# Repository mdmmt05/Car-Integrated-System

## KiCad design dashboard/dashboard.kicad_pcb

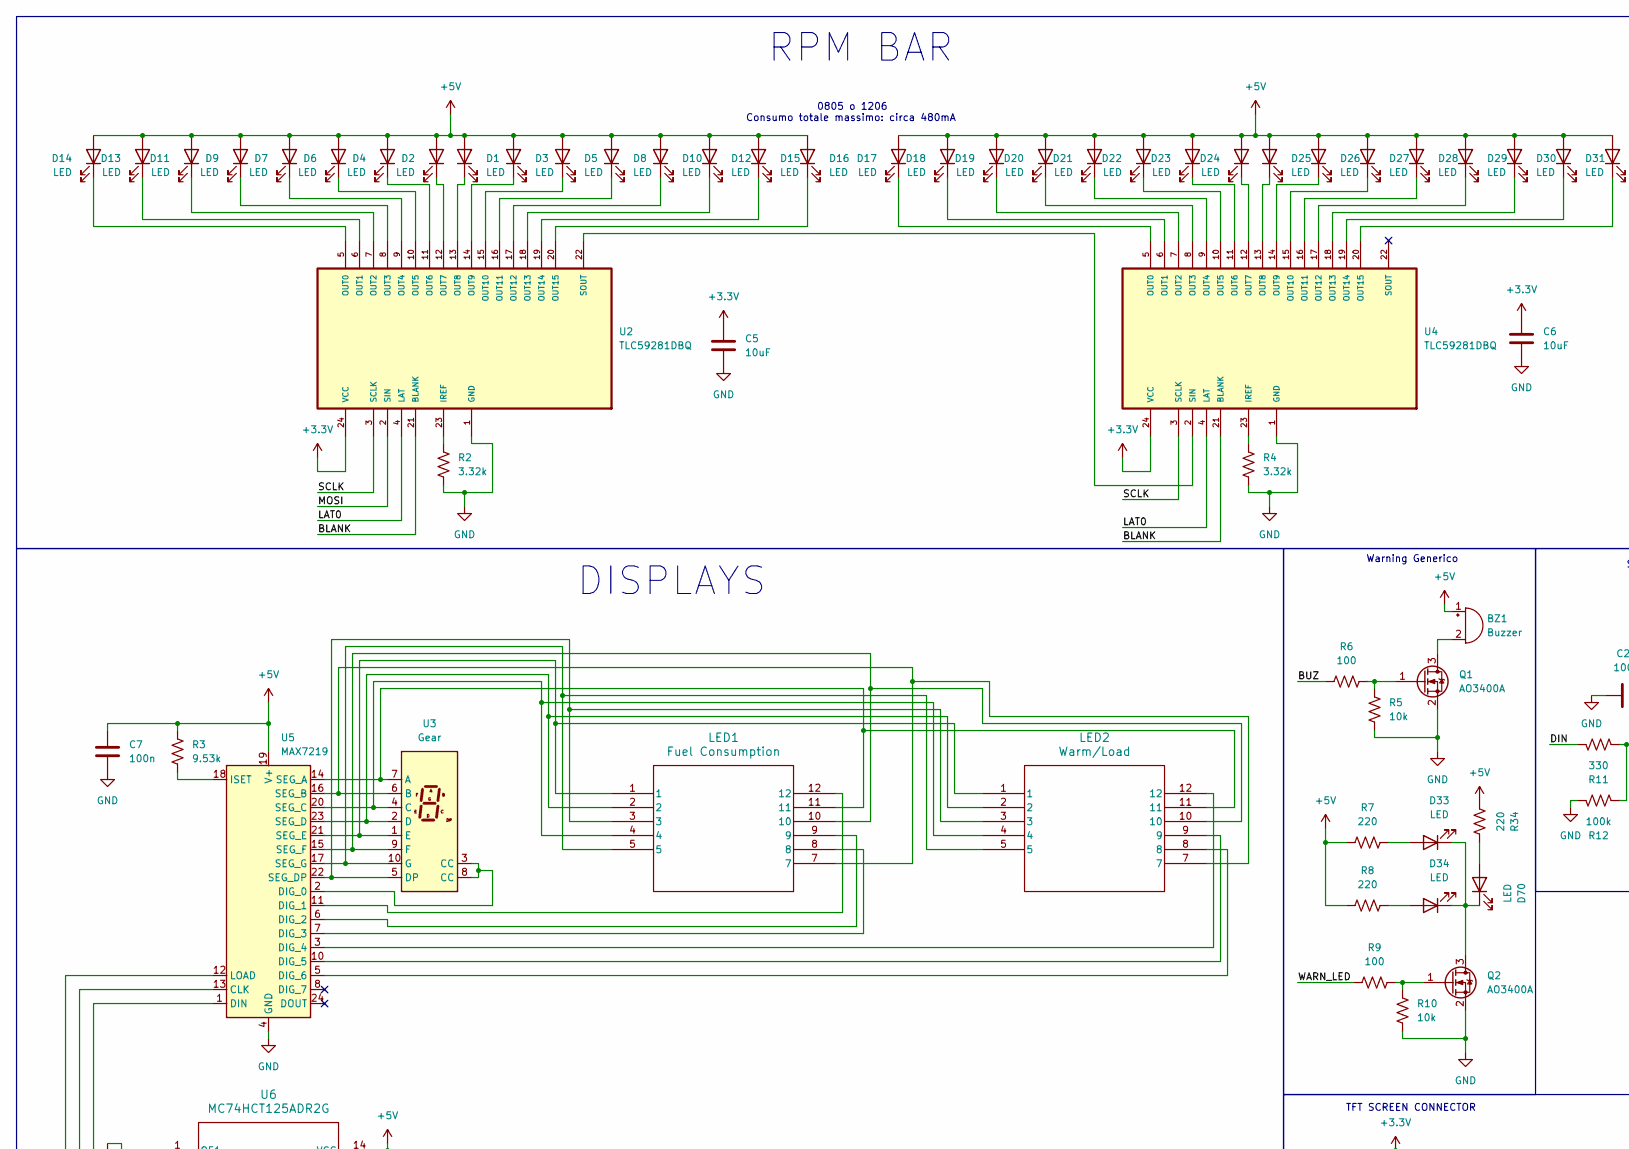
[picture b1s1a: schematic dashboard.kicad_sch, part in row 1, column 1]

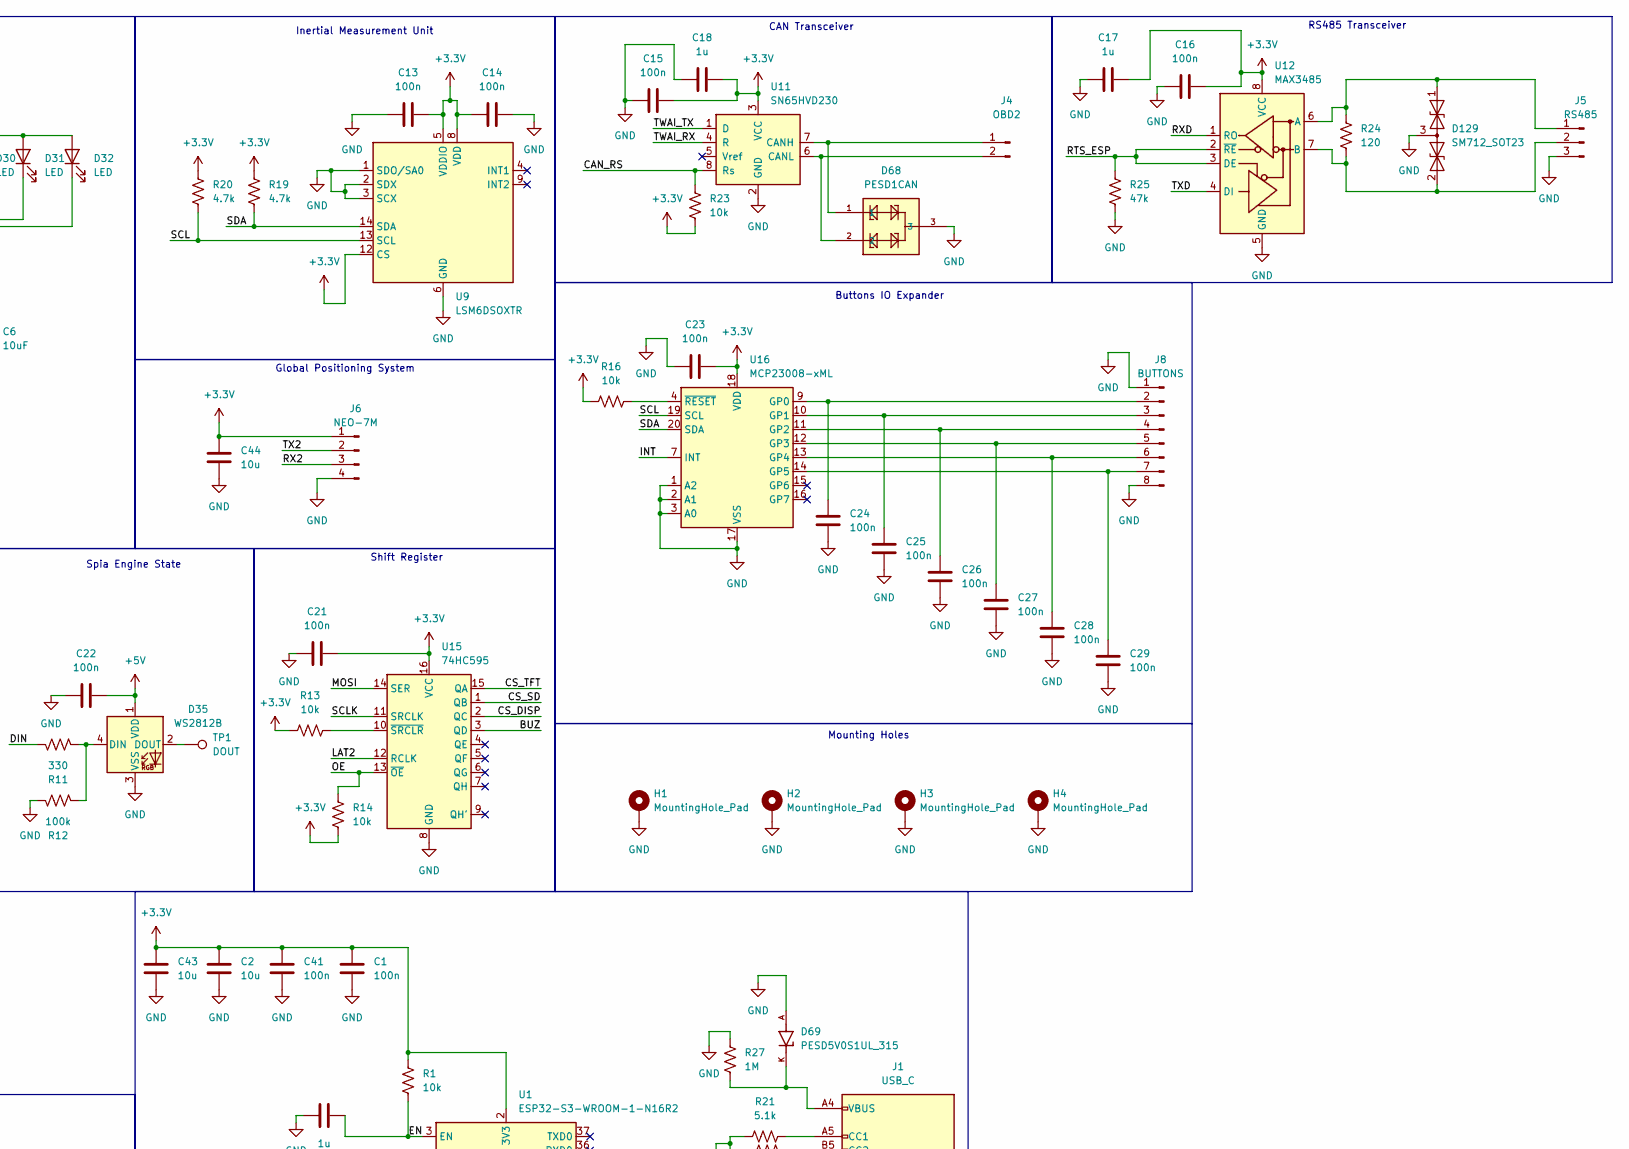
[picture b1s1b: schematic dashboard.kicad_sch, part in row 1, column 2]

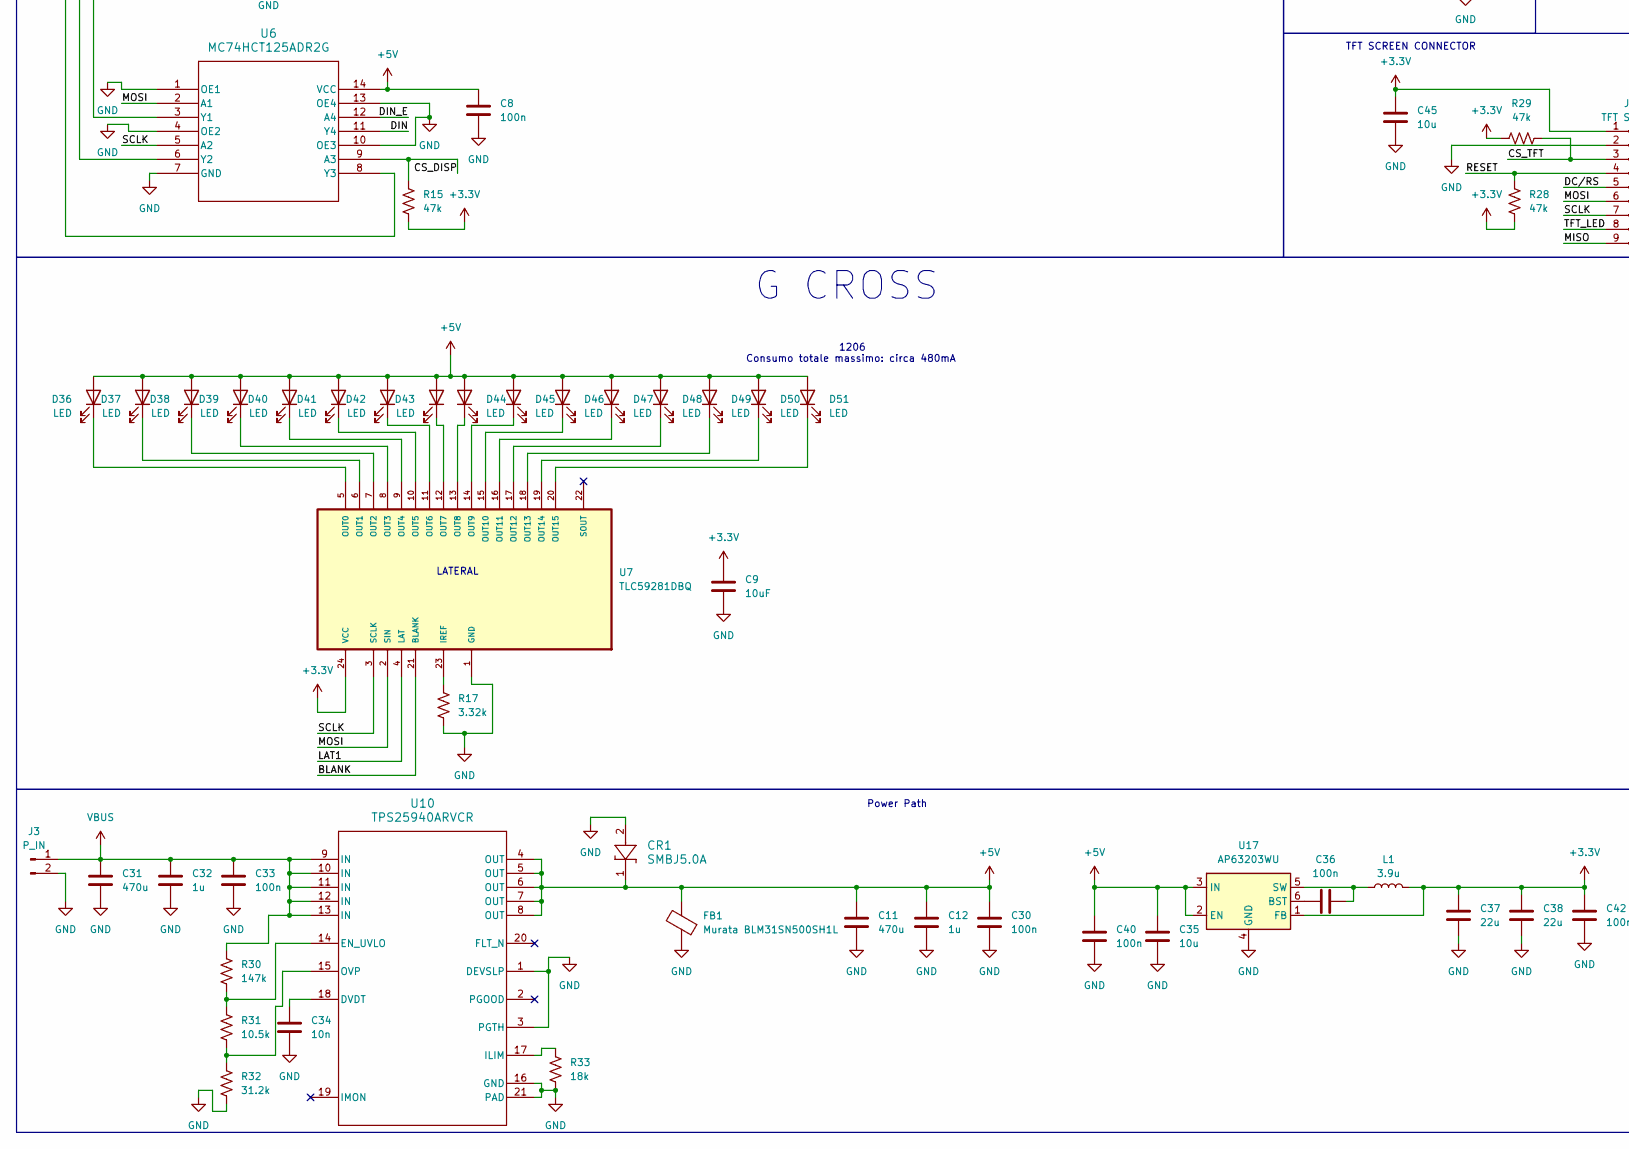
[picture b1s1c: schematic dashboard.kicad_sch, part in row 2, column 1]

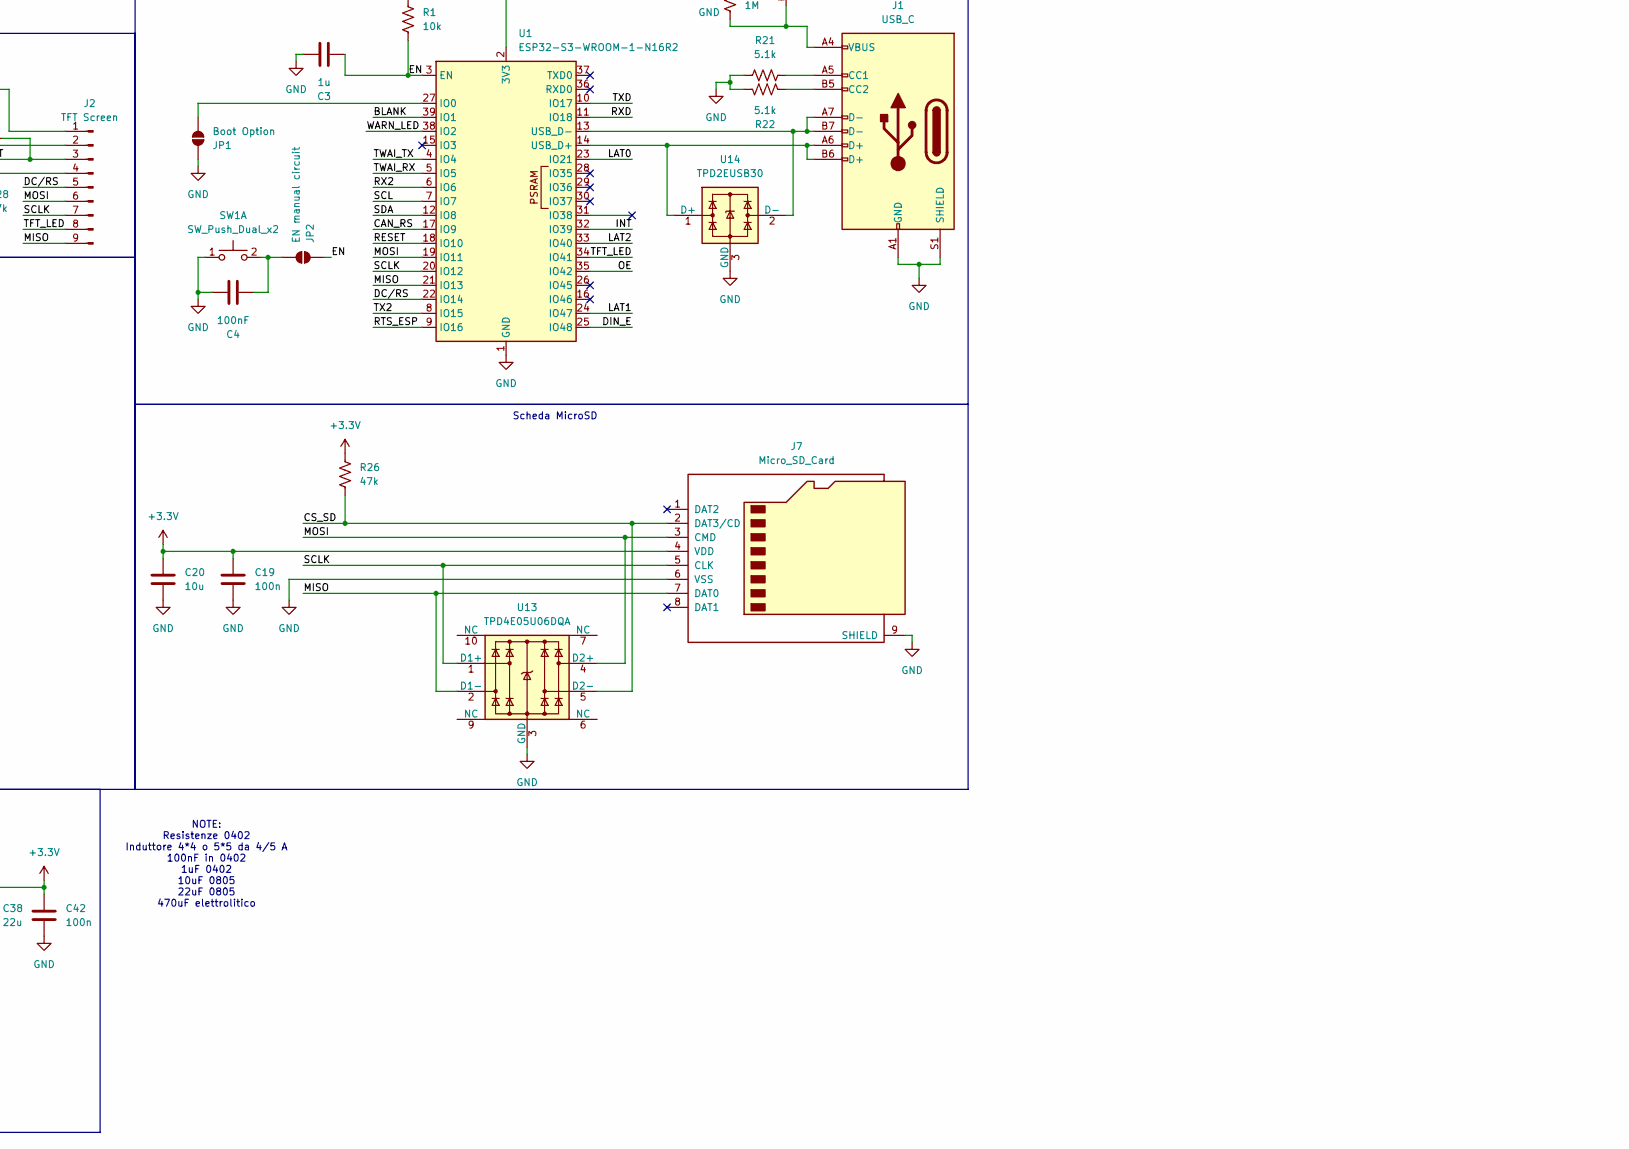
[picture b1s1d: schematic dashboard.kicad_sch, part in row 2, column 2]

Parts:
BZ1: Buzzer; Buzzer_12x9.5RM7.6
C1, C7, C8, C13, C14, C15, C16, C19, C21, C22, C23, C24, C25, C26, C27, C28, C29, C30, C33, C36, C40, C41, C42: 100n; C_0402_1005Metric
C2, C20, C35, C43, C44, C45: 10u; C_0805_2012Metric
C3, C12, C17, C18, C32: 1u; C_0402_1005Metric
C4: 100nF; C_0402_1005Metric
C5, C6, C9: 10uF; C_0805_2012Metric
C11, C31: 470u; CP_Elec_6.3x7.7
C34: 10n; C_0402_1005Metric
C37, C38: 22u; C_0805_2012Metric
CR1: SMBJ5.0A; D_SMB
D1, D2, D3, D4, D5, D6, D7, D8, D9, D10, D11, D12, D13, D14, D15, D16, D17, D18, D19, D20, D21, D22, D23, D24, D25, D26, D27, D28, D29, D30, D31, D32, D33, D34, D36, D37, D38, D39, D40, D41, D42, D43, D44, D45, D46, D47, D48, D49, D50, D51, D70: LED; LED_1206_3216Metric
D35: WS2812B; LED_WS2812B_PLCC4_5.0x5.0mm_P3.2mm
D68: PESD1CAN; SOT-23
D69: PESD5V0S1UL_315; DIO_PESD5V0S1UL_315
D129: SM712_SOT23; SOT-23
FB1: Murata BLM31SN500SH1L; C_1206_3216Metric
H1, H2, H3, H4: MountingHole_Pad; MountingHole_4.3mm_M4_Pad_Via
J1: USB_C; USB_C_Receptacle_JAE_DX07S016JA1R1500
J2: TFT Screen; PinHeader_1x09_P2.54mm_Vertical
J3: P_IN; TerminalBlock_MaiXu_MX126-5.0-02P_1x02_P5.00mm
J4: OBD2; TerminalBlock_MaiXu_MX126-5.0-02P_1x02_P5.00mm
J5: RS485; TerminalBlock_MaiXu_MX126-5.0-03P_1x03_P5.00mm
J6: NEO-7M; PinHeader_1x04_P2.54mm_Vertical
J7: Micro_SD_Card; microSD_HC_Molex_104031-0811
J8: BUTTONS; JST_XH_S8B-XH-A_1x08_P2.50mm_Horizontal
JP1: Boot Option; PinHeader_1x02_P2.54mm_Vertical
JP2: EN manual circuit; PinHeader_1x02_P2.54mm_Vertical
L1: 3.9u; L_Cenker_CKCS6045
LED1: Fuel Consumption; ZHIHAO FJ5361BH
LED2: Warm/Load; ZHIHAO FJ5361BH
Q1, Q2: AO3400A; SOT-23
R1, R5, R10, R13, R14, R16, R23: 10k; R_0402_1005Metric
R2, R4, R17: 3.32k; R_0402_1005Metric
R3: 9.53k; R_0402_1005Metric
R6, R9: 100; R_0402_1005Metric
R7, R8, R34: 220; R_0402_1005Metric
R11: 330; R_0402_1005Metric
R12: 100k; R_0402_1005Metric
R15, R25, R26, R28, R29: 47k; R_0402_1005Metric
R19, R20: 4.7k; R_0402_1005Metric
R21, R22: 5.1k; R_0402_1005Metric
R24: 120; R_0402_1005Metric
R27: 1M; R_0402_1005Metric
R30: 147k; R_0402_1005Metric
R31: 10.5k; R_0402_1005Metric
R32: 31.2k; R_0402_1005Metric
R33: 18k; R_0402_1005Metric
SW1: SW_Push_Dual_x2; SW_PUSH_6mm
TP1: DOUT; TestPoint_Pad_D2.0mm
U1: ESP32-S3-WROOM-1-N16R2; ESP32-S3-WROOM-1
U2, U4, U7: TLC59281DBQ; DBQ24; MPN TLC59281DBQ
U3: Gear; ARKLED SM411006N_15
U5: MAX7219; 21-0042_W24&plus_1_MXM
U6: MC74HCT125ADR2G; SOIC-14_NB_ONS
U9: LSM6DSOXTR; LGA-14_3x2.5mm_P0.5mm_LayoutBorder3x4y
U10: TPS25940ARVCR; RVC0020A
U11: SN65HVD230; SOIC-8_3.9x4.9mm_P1.27mm
U12: MAX3485; SOIC-8_3.9x4.9mm_P1.27mm
U13: TPD4E05U06DQA; USON-10_2.5x1.0mm_P0.5mm
U14: TPD2EUSB30; Texas_DRT-3
U15: 74HC595; SOIC127P600X175-16N
U16: MCP23008-xML; QFN-20-1EP_4x4mm_P0.5mm_EP2.7x2.7mm
U17: AP63203WU; TSOT-23-6

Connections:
+3.3V: C1.2, C2.2, C5.1, C6.1, C9.1, C13.2, C14.1, C15.2, C16.2, C17.2, C18.2, C19.1, C20.1, C21.2, C23.2, C37.1, C38.1, C41.2, C42.1, C43.2, C44.2, C45.2, J2.1, J6.1, J7.4 (VDD), L1.2, R1.2, R13.1, R14.1, R15.2, R16.1, R19.1, R20.1, R23.2, R26.1, R28.2, R29.1, U1.2 (3V3), U2.24 (VCC), U4.24 (VCC), U7.24 (VCC), U9.5 (VDDIO), U9.8 (VDD), U9.12 (CS), U11.3 (VCC), U12.8 (VCC), U15.16 (VCC), U16.18 (VDD), U17.1 (FB)
+5V: BZ1.1 (+), C7.1, C8.1, C11.1, C12.1, C22.2, C30.1, C35.1, C40.1, CR1.1, D1.2 (A), D2.2 (A), D3.2 (A), D4.2 (A), D5.2 (A), D6.2 (A), D7.2 (A), D8.2 (A), D9.2 (A), D10.2 (A), D11.2 (A), D12.2 (A), D13.2 (A), D14.2 (A), D15.2 (A), D16.2 (A), D17.2 (A), D18.2 (A), D19.2 (A), D20.2 (A), D21.2 (A), D22.2 (A), D23.2 (A), D24.2 (A), D25.2 (A), D26.2 (A), D27.2 (A), D28.2 (A), D29.2 (A), D30.2 (A), D31.2 (A), D32.2 (A), D35.1 (VDD), D36.2 (A), D37.2 (A), D38.2 (A), D39.2 (A), D40.2 (A), D41.2 (A), D42.2 (A), D43.2 (A), D44.2 (A), D45.2 (A), D46.2 (A), D47.2 (A), D48.2 (A), D49.2 (A), D50.2 (A), D51.2 (A), FB1.2, R3.1, R7.1, R8.1, R34.1, U5.19 (V+), U6.14 (VCC), U10.4 (OUT), U10.5 (OUT), U10.6 (OUT), U10.7 (OUT), U10.8 (OUT), U17.2 (EN), U17.3 (IN)
/BLANK: U1.39 (IO1), U2.21 (BLANK), U4.21 (BLANK), U7.21 (BLANK)
/BUZ: R6.1, U15.3 (QD)
/CAN_RS: R23.1, U1.17 (IO9), U11.8 (Rs)
/CS_DISP: R15.1, U6.9 (A3), U15.2 (QC)
/CS_SD: J7.2 (DAT3/CD), R26.2, U13.5 (D2-), U15.1 (QB)
/CS_TFT: J2.3, R29.2, U15.15 (QA)
/DC/RS: J2.5, U1.22 (IO14)
/DIN: R11.1, U6.11 (Y4)
/DIN_E: U1.25 (IO48), U6.12 (A4)
/EN: C3.1, JP2.1 (A), R1.1, U1.3 (EN)
/INT: U1.32 (IO39), U16.7 (INT)
/LAT0: U1.23 (IO21), U2.4 (LAT), U4.4 (LAT)
/LAT1: U1.24 (IO47), U7.4 (LAT)
/LAT2: U1.33 (IO40), U15.12 (RCLK)
/MISO: J2.9, J7.7 (DAT0), U1.21 (IO13), U13.2 (D1-)
/MOSI: J2.6, J7.3 (CMD), U1.19 (IO11), U2.2 (SIN), U6.2 (A1), U7.2 (SIN), U13.4 (D2+), U15.14 (SER)
/OE: R14.2, U1.35 (IO42), U15.13 (~OE)
/RESET: J2.4, R28.1, U1.18 (IO10)
/RTS_ESP: R25.1, U1.9 (IO16), U12.2 (~RE), U12.3 (DE)
/RX2: J6.3, U1.6 (IO6)
/RXD: U1.11 (IO18), U12.1 (RO)
/SCL: R20.2, U1.7 (IO7), U9.13 (SCL), U16.19 (SCL)
/SCLK: J2.7, J7.5 (CLK), U1.20 (IO12), U2.3 (SCLK), U4.3 (SCLK), U6.5 (A2), U7.3 (SCLK), U13.1 (D1+), U15.11 (SRCLK)
/SDA: R19.2, U1.12 (IO8), U9.14 (SDA), U16.20 (SDA)
/TFT_LED: J2.8, U1.34 (IO41)
/TWAI_RX: U1.5 (IO5), U11.4 (R)
/TWAI_TX: U1.4 (IO4), U11.1 (D)
/TX2: J6.2, U1.8 (IO15)
/TXD: U1.10 (IO17), U12.4 (DI)
/WARN_LED: R9.1, U1.38 (IO2)
GND: C1.1, C2.1, C3.2, C4.2, C5.2, C6.2, C7.2, C8.2, C9.2, C11.2, C12.2, C13.1, C14.2, C15.1, C16.1, C17.1, C18.1, C19.2, C20.2, C21.1, C22.1, C23.1, C24.1, C25.1, C26.1, C27.1, C28.1, C29.1, C30.2, C31.2, C32.2, C33.2, C34.2, C35.2, C37.2, C38.2, C40.2, C41.1, C42.2, C43.1, C44.1, C45.1, CR1.2, D35.3 (VSS), D68.3, D69.A, D129.3 (common), FB1.1, H1.1, H2.1, H3.1, H4.1, J1.A1 (GND), J1.A12 (GND), J1.B1 (GND), J1.B12 (GND), J1.S1 (SHIELD), J2.2, J3.2, J5.3, J6.4, J7.6 (VSS), J7.9 (SHIELD), J8.1, J8.8, JP1.1 (A), Q1.2 (S), Q2.2 (S), R2.2, R4.2, R5.2, R10.2, R12.1, R17.2, R21.1, R22.1, R25.2, R27.1, R32.2, R33.2, SW1.1 (C), U1.1 (GND), U1.40 (GND), U1.41 (GND), U2.1 (GND), U4.1 (GND), U5.4 (GND), U5.9 (GND), U6.1 (OE1), U6.4 (OE2), U6.7 (GND), U6.10 (OE3), U6.13 (OE4), U7.1 (GND), U9.1 (SDO/SA0), U9.2 (SDX), U9.3 (SCX), U9.6 (GND), U9.7 (GND), U10.1 (DEVSLP), U10.3 (PGTH), U10.16 (GND), U10.21 (PAD), U10.V, U11.2 (GND), U12.5 (GND), U13.3 (GND), U13.8 (GND), U14.3 (GND), U15.8 (GND), U16.1 (A2), U16.2 (A1), U16.3 (A0), U16.17 (VSS), U17.4 (GND)
unnamed: BZ1.2 (-), Q1.3 (D)
unnamed: D1.1 (K), U2.13 (OUT8)
unnamed: D2.1 (K), U2.12 (OUT7)
unnamed: D3.1 (K), U2.14 (OUT9)
unnamed: D4.1 (K), U2.11 (OUT6)
unnamed: D5.1 (K), U2.15 (OUT10)
unnamed: D6.1 (K), U2.10 (OUT5)
unnamed: D7.1 (K), U2.9 (OUT4)
unnamed: D8.1 (K), U2.16 (OUT11)
unnamed: D9.1 (K), U2.8 (OUT3)
unnamed: D10.1 (K), U2.17 (OUT12)
unnamed: D11.1 (K), U2.7 (OUT2)
unnamed: D12.1 (K), U2.18 (OUT13)
unnamed: D13.1 (K), U2.6 (OUT1)
unnamed: D14.1 (K), U2.5 (OUT0)
unnamed: D15.1 (K), U2.19 (OUT14)
unnamed: D16.1 (K), U2.20 (OUT15)
unnamed: D17.1 (K), U4.5 (OUT0)
unnamed: D18.1 (K), U4.6 (OUT1)
unnamed: D19.1 (K), U4.7 (OUT2)
unnamed: D20.1 (K), U4.8 (OUT3)
unnamed: D21.1 (K), U4.9 (OUT4)
unnamed: D22.1 (K), U4.10 (OUT5)
unnamed: D23.1 (K), U4.11 (OUT6)
unnamed: D24.1 (K), U4.12 (OUT7)
unnamed: D25.1 (K), U4.13 (OUT8)
unnamed: D26.1 (K), U4.14 (OUT9)
unnamed: D27.1 (K), U4.15 (OUT10)
unnamed: D28.1 (K), U4.16 (OUT11)
unnamed: D29.1 (K), U4.17 (OUT12)
unnamed: D30.1 (K), U4.18 (OUT13)
unnamed: D31.1 (K), U4.19 (OUT14)
unnamed: D32.1 (K), U4.20 (OUT15)
unnamed: D33.2 (A), R7.2
unnamed: D33.1 (K), D34.1 (K), D70.1 (K), Q2.3 (D)
unnamed: D34.2 (A), R8.2
unnamed: D35.4 (DIN), R11.2, R12.2
unnamed: D35.2 (DOUT), TP1.1
unnamed: D36.1 (K), U7.5 (OUT0)
unnamed: D37.1 (K), U7.6 (OUT1)
unnamed: D38.1 (K), U7.7 (OUT2)
unnamed: D39.1 (K), U7.8 (OUT3)
unnamed: D40.1 (K), U7.9 (OUT4)
unnamed: D41.1 (K), U7.10 (OUT5)
unnamed: D42.1 (K), U7.11 (OUT6)
unnamed: D43.1 (K), U7.12 (OUT7)
unnamed: D44.1 (K), U7.13 (OUT8)
unnamed: D45.1 (K), U7.14 (OUT9)
unnamed: D46.1 (K), U7.15 (OUT10)
unnamed: D47.1 (K), U7.16 (OUT11)
unnamed: D48.1 (K), U7.17 (OUT12)
unnamed: D49.1 (K), U7.18 (OUT13)
unnamed: D50.1 (K), U7.19 (OUT14)
unnamed: D51.1 (K), U7.20 (OUT15)
unnamed: D69.K, J1.A4 (VBUS), J1.A9 (VBUS), J1.B4 (VBUS), J1.B9 (VBUS), R27.2
unnamed: D70.2 (A), R34.2
unnamed: D129.1 (A1), J5.1, R24.1, U12.6 (A)
unnamed: D129.2 (A2), J5.2, R24.2, U12.7 (B)
unnamed: J1.A5 (CC1), R21.2
unnamed: J1.B5 (CC2), R22.2
unnamed: D68.1, J4.1, U11.7 (CANH)
unnamed: D68.2, J4.2, U11.6 (CANL)
unnamed: C24.2, J8.2, U16.9 (GP0)
unnamed: C25.2, J8.3, U16.10 (GP1)
unnamed: C26.2, J8.4, U16.11 (GP2)
unnamed: C27.2, J8.5, U16.12 (GP3)
unnamed: C28.2, J8.6, U16.13 (GP4)
unnamed: C29.2, J8.7, U16.14 (GP5)
unnamed: JP1.2 (B), U1.27 (IO0)
unnamed: C4.1, JP2.2 (B), SW1.2 (D)
unnamed: Q1.1 (G), R5.1, R6.2
unnamed: Q2.1 (G), R9.2, R10.1
unnamed: J1.A6 (D+), J1.B6 (D+), U1.14 (USB_D+), U14.1 (D+)
unnamed: J1.A7 (D-), J1.B7 (D-), U1.13 (USB_D-), U14.2 (D-)
unnamed: R2.1, U2.23 (IREF)
unnamed: U2.22 (SOUT), U4.2 (SIN)
unnamed: LED1.11, LED2.11, U3.7 (A), U5.14 (SEG_A)
unnamed: LED1.7, LED2.7, U3.6 (B), U5.16 (SEG_B)
unnamed: LED1.4, LED2.4, U3.4 (C), U5.20 (SEG_C)
unnamed: LED1.2, LED2.2, U3.2 (D), U5.23 (SEG_D)
unnamed: LED1.3, LED2.3, U3.5 (DP), U5.22 (SEG_DP)
unnamed: LED1.1, LED2.1, U3.1 (E), U5.21 (SEG_E)
unnamed: LED1.10, LED2.10, U3.9 (F), U5.15 (SEG_F)
unnamed: LED1.5, LED2.5, U3.10 (G), U5.17 (SEG_G)
unnamed: R4.1, U4.23 (IREF)
unnamed: U5.13 (CLK), U6.6 (Y2)
unnamed: U3.3 (CC), U3.8 (CC), U5.2 (DIG_0)
unnamed: LED1.12, U5.11 (DIG_1)
unnamed: LED1.9, U5.6 (DIG_2)
unnamed: LED1.8, U5.7 (DIG_3)
unnamed: LED2.12, U5.3 (DIG_4)
unnamed: LED2.9, U5.10 (DIG_5)
unnamed: LED2.8, U5.5 (DIG_6)
unnamed: U5.1 (DIN), U6.3 (Y1)
unnamed: R3.2, U5.18 (ISET)
unnamed: U5.12 (LOAD), U6.8 (Y3)
unnamed: R17.1, U7.23 (IREF)
unnamed: C34.1, U10.18 (DVDT)
unnamed: R30.2, R31.1, U10.14 (EN_UVLO)
unnamed: R33.1, U10.17 (ILIM)
unnamed: R31.2, R32.1, U10.15 (OVP)
unnamed: R13.2, U15.10 (~SRCLR)
unnamed: R16.2, U16.4 (~RESET)
unnamed: C36.1, U17.6 (BST)
unnamed: C36.2, L1.1, U17.5 (SW)
VBUS: C31.1, C32.1, C33.1, J3.1, R30.1, U10.9 (IN), U10.10 (IN), U10.11 (IN), U10.12 (IN), U10.13 (IN)

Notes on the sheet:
Consumo totale massimo: circa 480mA
Spia Engine State
Warning Generico
RS485 Transceiver
NOTE: Resistenze 0402 Induttore 4*4 o 5*5 da 4/5 A 100nF in 0402 1uF 0402 10uF 0805 22uF 0805 470uF elettrolitico
Global Positioning System
DISPLAYS
Buttons IO Expander
CAN Transceiver
1206
Power Path
Mounting Holes
RPM BAR
Scheda MicroSD
TFT SCREEN CONNECTOR
Shift Register
Inertial Measurement Unit
G CROSS
0805 o 1206
LATERAL

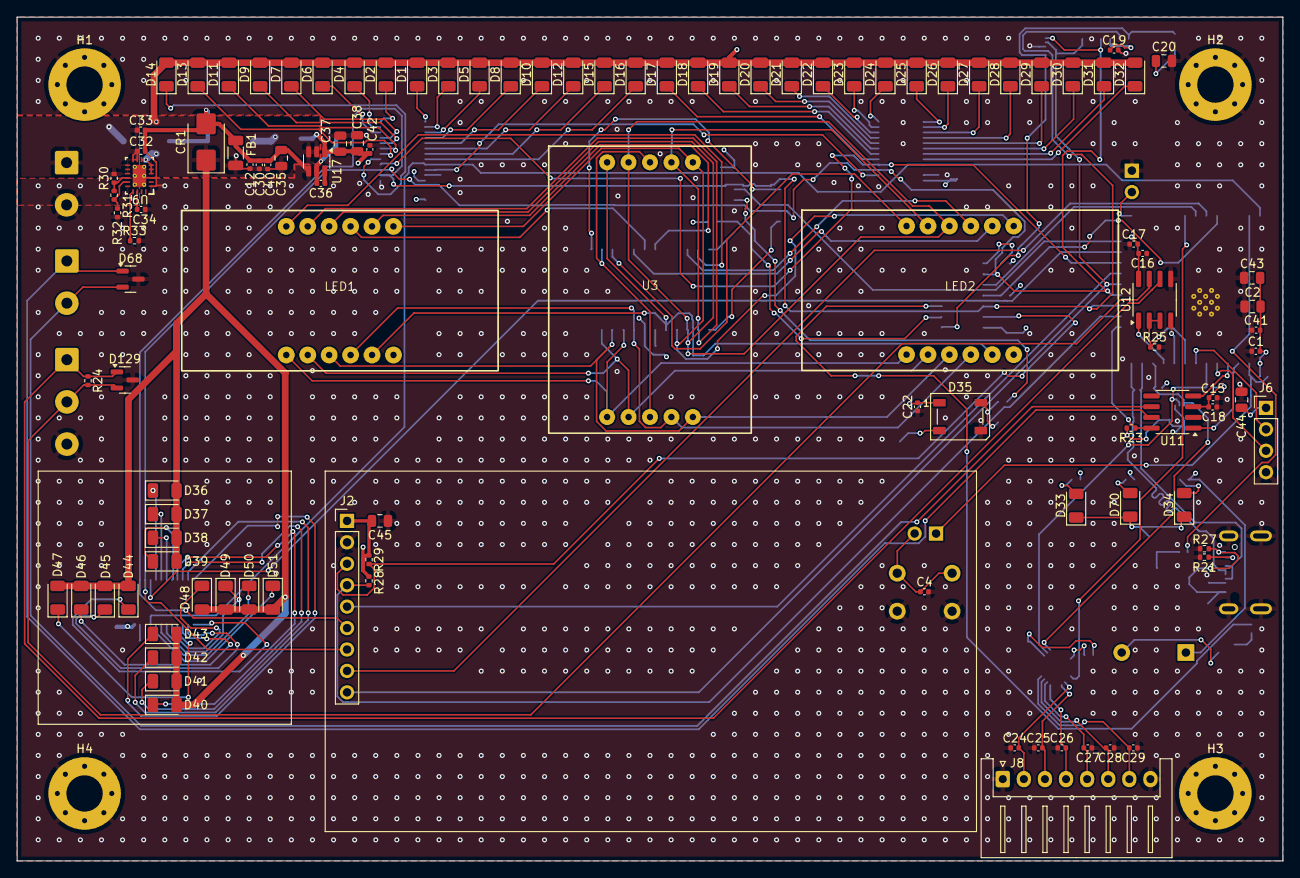
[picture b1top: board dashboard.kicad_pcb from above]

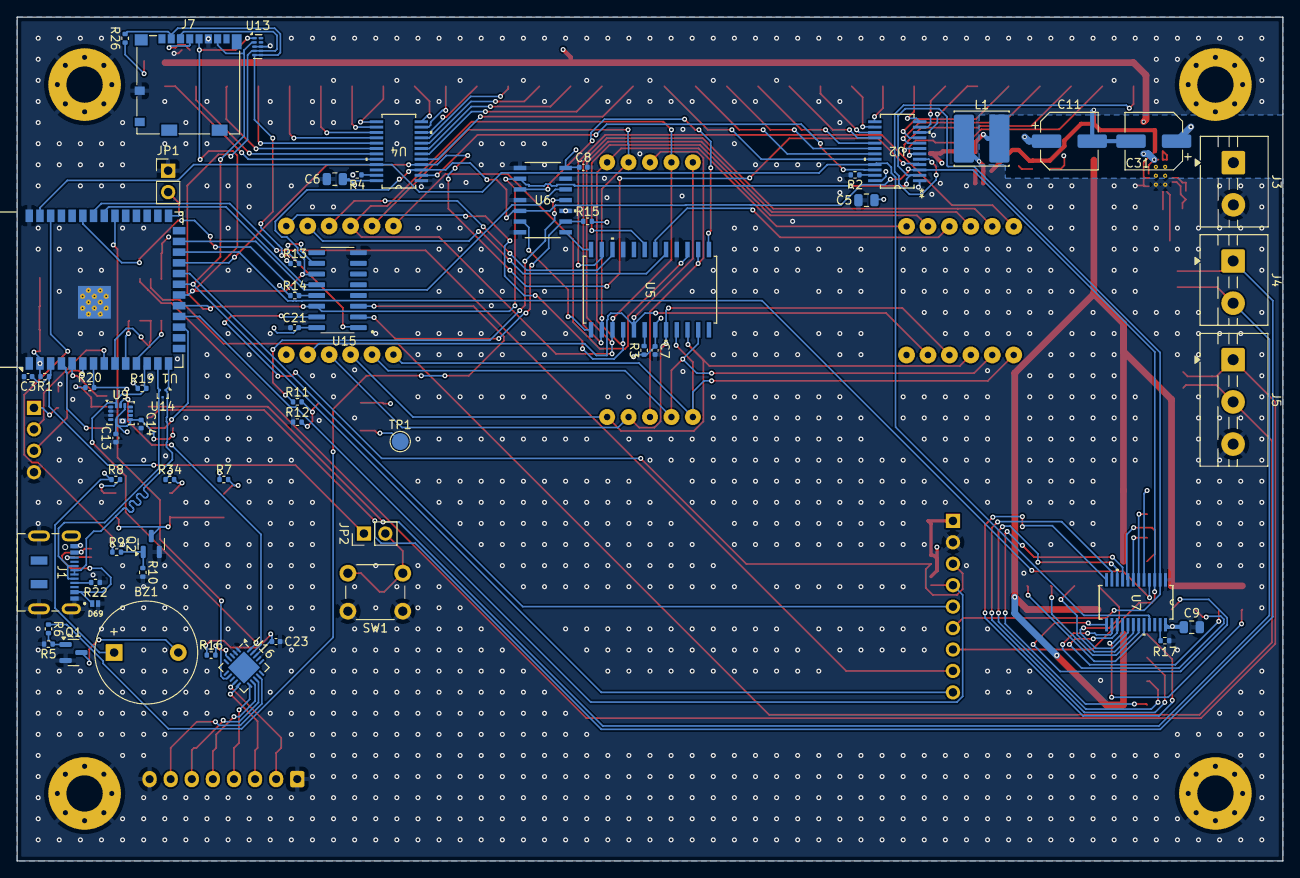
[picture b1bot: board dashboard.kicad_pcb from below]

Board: 4 copper layers, 150.0 x 100.0 mm, 171 parts (59 on the bottom side), 139 nets.

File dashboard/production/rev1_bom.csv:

Designator,Footprint,Quantity,Value,LCSC Part #
BZ1,Buzzer_12x9.5RM7.6,1,Buzzer,
"C1, C13, C14, C15, C16, C19, C21, C22, C23, C24, C25, C26, C27, C28, C29, C30, C33, C36, C40, C41, C42, C7, C8",0402,23,100n,
"C11, C31",CP_Elec_6.3x7.7,2,470u,
"C12, C17, C18, C3, C32",0402,5,1u,
"C2, C20, C35, C43, C44, C45",0805,6,10u,
C34,0402,1,10n,
"C37, C38",0805,2,22u,
C4,0402,1,100nF,
"C5, C6, C9",0805,3,10uF,
CR1,D_SMB,1,SMBJ5.0A,
"D1, D10, D11, D12, D13, D14, D15, D16, D17, D18, D19, D2, D20, D21, D22, D23, D24, D25, D26, D27, D28, D29, D3, D30, D31, D32, D33, D34, D36, D37, D38, D39, D4, D40, D41, D42, D43, D44, D45, D46, D47, D48, D49, D5, D50, D51, D6, D7, D70, D8, D9",1206,51,LED,
D129,SOT-23,1,SM712_SOT23,
D35,LED_WS2812B_PLCC4_5.0x5.0mm_P3.2mm,1,WS2812B,
D68,SOT-23,1,PESD1CAN,
D69,DIO_PESD5V0S1UL_315,1,PESD5V0S1UL_315,
FB1,1206,1,Murata BLM31SN500SH1L,
J1,USB_C_Receptacle_JAE_DX07S016JA1R1500,1,USB_C,
J2,PinHeader_1x09_P2.54mm_Vertical,1,TFT Screen,
J3,TerminalBlock_MaiXu_MX126-5.0-02P_1x02_P5.00mm,1,P_IN,
J4,TerminalBlock_MaiXu_MX126-5.0-02P_1x02_P5.00mm,1,OBD2,
J5,TerminalBlock_MaiXu_MX126-5.0-03P_1x03_P5.00mm,1,RS485,
J6,PinHeader_1x04_P2.54mm_Vertical,1,NEO-7M,
J7,microSD_HC_Molex_104031-0811,1,Micro_SD_Card,
J8,JST_XH_S8B-XH-A_1x08_P2.50mm_Horizontal,1,BUTTONS,
L1,L_Cenker_CKCS6045,1,3.9u,
LED1,ZHIHAO FJ5361BH,1,Fuel Consumption,
LED2,ZHIHAO FJ5361BH,1,Warm/Load,
"Q1, Q2",SOT-23,2,AO3400A,
"R1, R10, R13, R14, R16, R23, R5",0402,7,10k,
R11,0402,1,330,
R12,0402,1,100k,
"R15, R25, R26, R28, R29",0402,5,47k,
"R17, R2, R4",0402,3,3.32k,
"R19, R20",0402,2,4.7k,
"R21, R22",0402,2,5.1k,
R24,0402,1,120,
R27,0402,1,1M,
R3,0402,1,9.53k,
R30,0402,1,147k,
R31,0402,1,10.5k,
R32,0402,1,31.2k,
R33,0402,1,18k,
"R34, R7, R8",0402,3,220,
"R6, R9",0402,2,100,
SW1,SW_PUSH_6mm,1,SW_Push_Dual_x2,
TP1,TestPoint_Pad_D2.0mm,1,DOUT,
U1,ESP32-S3-WROOM-1,1,ESP32-S3-WROOM-1-N16R2,
U10,RVC0020A,1,TPS25940ARVCR,
U11,SOIC-8_3.9x4.9mm_P1.27mm,1,SN65HVD230,
U12,SOIC-8_3.9x4.9mm_P1.27mm,1,MAX3485,
U13,USON-10_2.5x1.0mm_P0.5mm,1,TPD4E05U06DQA,
U14,Texas_DRT-3,1,TPD2EUSB30,
U15,SOIC127P600X175-16N,1,74HC595,
U16,QFN-20-1EP_4x4mm_P0.5mm_EP2.7x2.7mm,1,MCP23008-xML,
U17,TSOT-23-6,1,AP63203WU,
"U2, U4, U7",DBQ24,3,TLC59281DBQ,TLC59281DBQ
U3,ARKLED SM411006N_15,1,Gear,
U5,21-0042_W24&plus_1_MXM,1,MAX7219,
U6,SOIC-14_NB_ONS,1,MC74HCT125ADR2G,
U9,LGA-14_3x2.5mm_P0.5mm_LayoutBorder3x4y,1,LSM6DSOXTR,

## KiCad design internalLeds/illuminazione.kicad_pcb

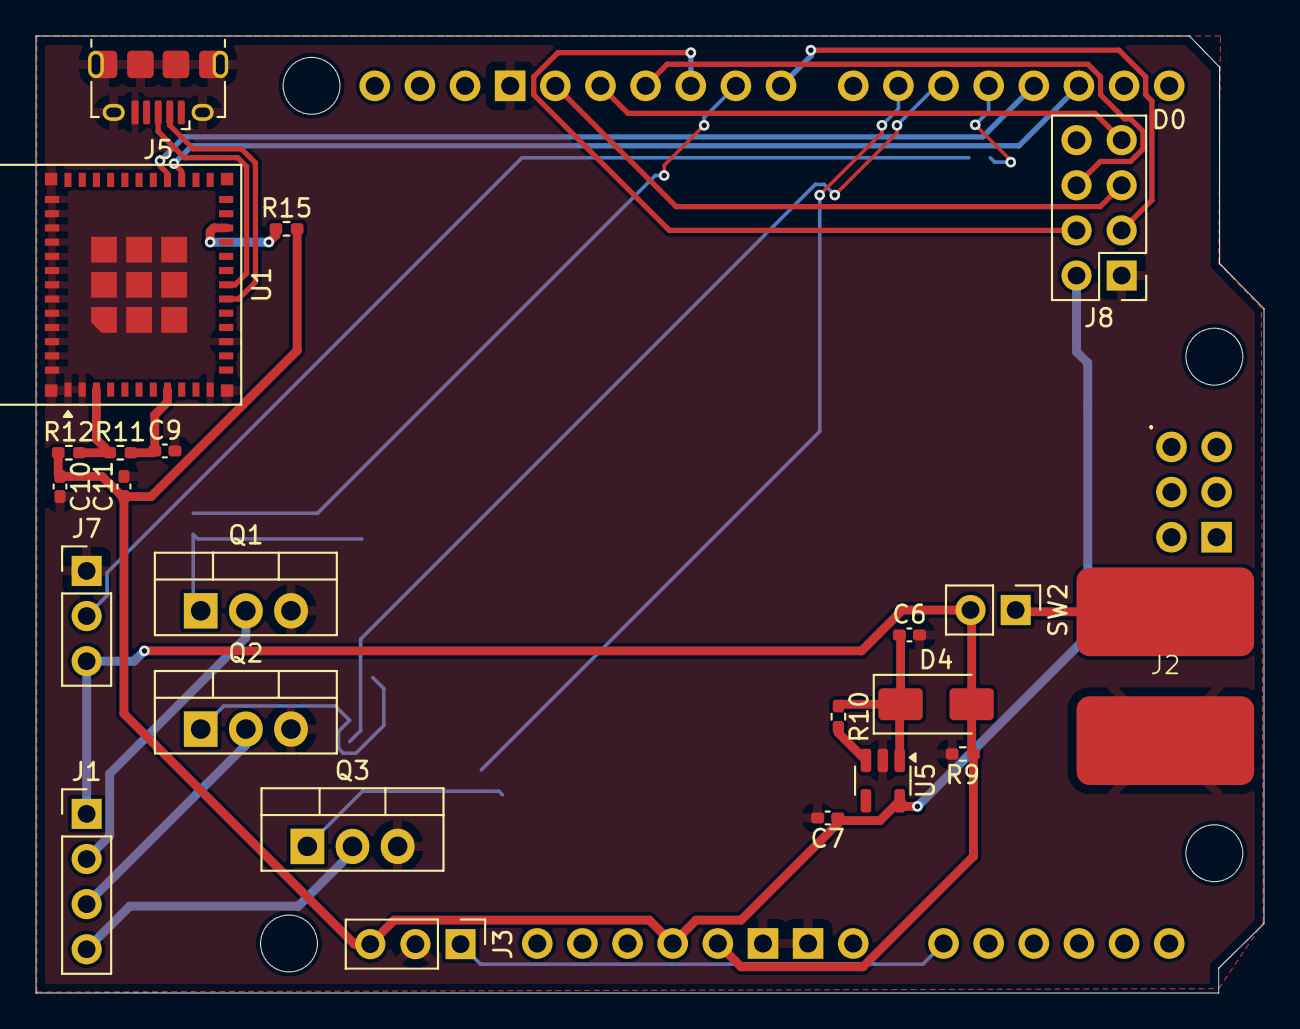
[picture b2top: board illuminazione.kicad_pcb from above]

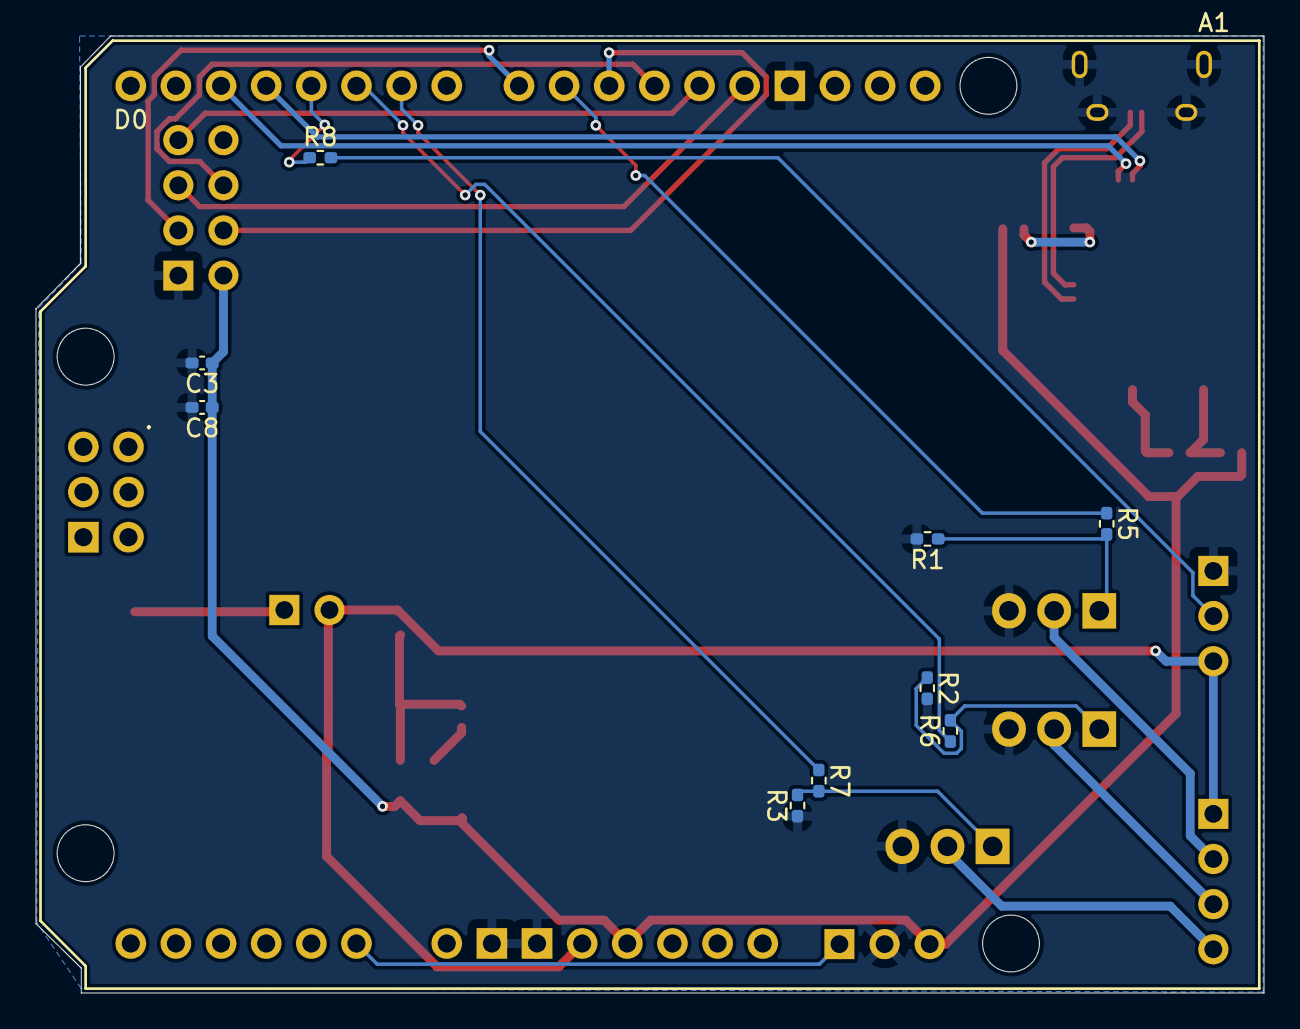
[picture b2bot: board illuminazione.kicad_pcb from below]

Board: 2 copper layers, 69.1 x 53.9 mm, 33 parts (9 on the bottom side), 30 nets.

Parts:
A1: Arduino_Uno_R3_Shield
C3: 100nF; C_0402_1005Metric_Pad0.74x0.62mm_HandSolder
C6, C7, C8: 10uF; C_0402_1005Metric_Pad0.74x0.62mm_HandSolder
C9, C10, C11: 1uF; C_0402_1005Metric_Pad0.74x0.62mm_HandSolder
D4: SS12; D_SMA
J1: Interior LEDs; PinHeader_1x04_P2.54mm_Vertical
J2: PowerIn; 2Pin-HighPower
J3: MAX4466; PinHeader_1x03_P2.54mm_Vertical
J5: USB_B_Micro; USB_Micro-B_Amphenol_10118194-0001LF_Horizontal
J7: Exterior LEDs; PinHeader_1x03_P2.54mm_Vertical
J8: Radio; PinHeader_2x04_P2.54mm_Vertical
Q1, Q2, Q3: IRLB8721PBF; TO-220-3_Vertical
R1, R2, R3, R11, R15: 10k; R_0402_1005Metric_Pad0.72x0.64mm_HandSolder
R5, R6, R7: 220; R_0402_1005Metric_Pad0.72x0.64mm_HandSolder
R8: 330; R_0402_1005Metric_Pad0.72x0.64mm_HandSolder
R9, R10: 100k; R_0402_1005Metric_Pad0.72x0.64mm_HandSolder
R12: 0; R_0402_1005Metric_Pad0.72x0.64mm_HandSolder
SW2: SW_DIP_x01; PinHeader_1x02_P2.54mm_Vertical
U1: ESP32-C6-MINI-1
U5: AP2112K-3.3; SOT-23-5

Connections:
+3.3V: A1.3V3 (3.3V), C3.1, C7.1, C8.1, C10.1, C11.1, J3.3, J8.2, R12.1, R15.2, U5.5 (VOUT)
+5V: A1.5V1 (5V), D4.2 (A), J1.1, J7.3, R9.1, SW2.2
B: A1.D6, R7.1
CE: A1.D8, J8.3
CSN: A1.D10 (D10_CS), J8.4
G: A1.D9, R5.1
GND: A1.GND1 (GND), A1.GND2 (GND), A1.GND3 (GND), C3.2, C6.2, C7.2, C8.2, C9.2, C10.2, C11.2, J2.2, J3.2, J5.5 (GND), J5.6 (Shield), J7.1, J8.1, Q1.3 (S), Q2.3 (S), Q3.3 (S), R1.2, R2.2, R3.1, R9.2, U1.1 (GND), U1.2 (GND), U1.11 (GND), U1.14 (GND), U1.36 (GND), U1.37 (GND), U1.38 (GND), U1.39 (GND), U1.40 (GND), U1.41 (GND), U1.42 (GND), U1.43 (GND), U1.44 (GND), U1.45 (GND), U1.46 (GND), U1.47 (GND), U1.48 (GND), U1.49 (GND), U1.50 (GND), U1.51 (GND), U1.52 (GND), U1.53 (GND), U5.2 (GND)
LED_DATA1: A1.D4, R8.1
MIC: A1.A0, J3.1
MISO: A1.D12, J8.7
MOSI: A1.D11, J8.6
unnamed: C6.1, D4.1 (K), R10.1, U5.1 (VIN)
unnamed: J1.3 (3Pin), Q2.2 (D)
unnamed: J1.2, Q1.2 (D)
unnamed: J1.4, Q3.2 (D)
unnamed: J2.1, SW2.1
unnamed: J7.2, R8.2
unnamed: Q1.1 (G), R1.1, R5.2
unnamed: Q2.1 (G), R2.1, R6.2
unnamed: Q3.1 (G), R3.2, R7.2
unnamed: R11.1, R12.2, U1.3 (3V3)
unnamed: C9.1, R11.2, U1.8 (EN)
unnamed: R15.1, U1.22 (IO8)
unnamed: R10.2, U5.3 (EN)
R: A1.D5, R6.1
SCK: A1.D13, J8.5
SF_RX: A1.D2 (D2_INT0), U1.27 (IO21)
SF_TX: A1.D3 (D3_INT1), U1.28 (IO22)
USB+: J5.3 (D+), U1.18 (IO13)
USB-: J5.2 (D-), U1.17 (IO12)

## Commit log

2025-12-02 Ligthing schematic update
2025-12-02 Aggiorna .gitignore
2025-12-03 Added RPM Indication System
2025-12-07 General Changes
2026-01-27 Rev. 2
